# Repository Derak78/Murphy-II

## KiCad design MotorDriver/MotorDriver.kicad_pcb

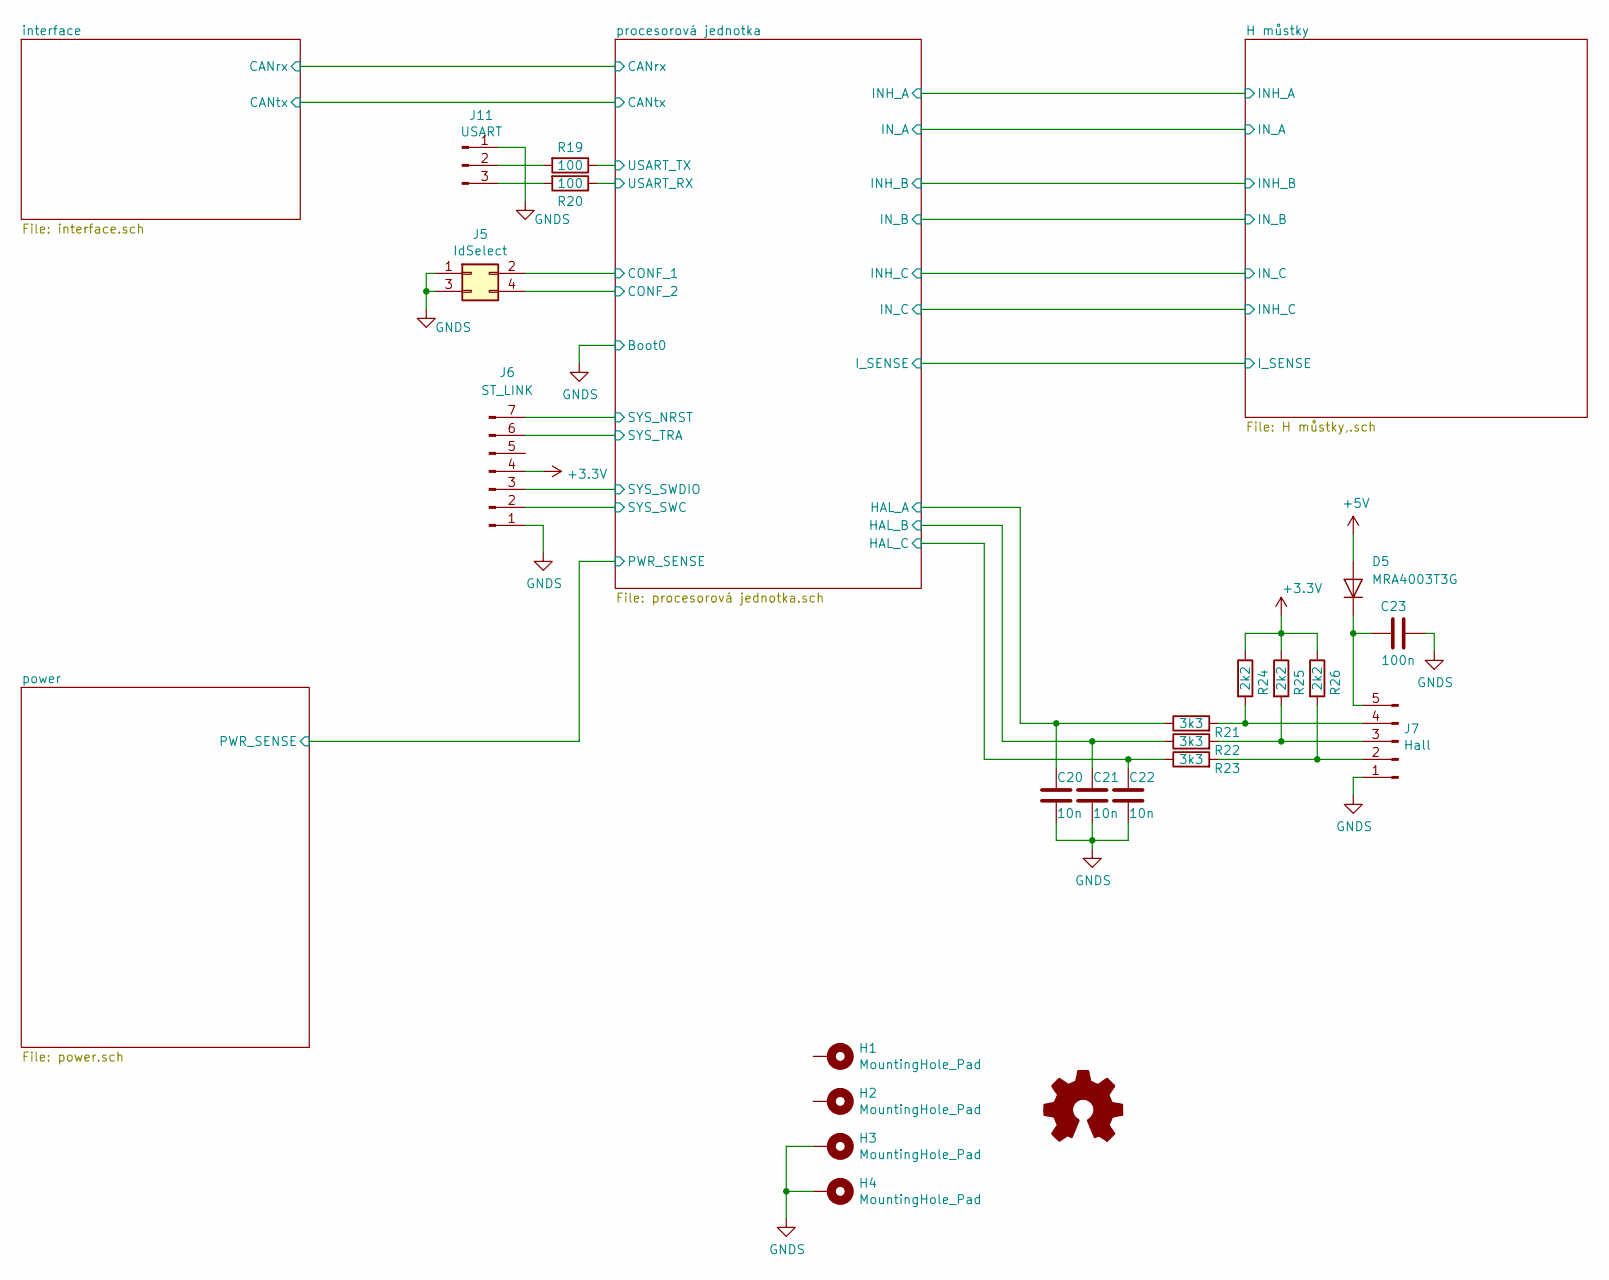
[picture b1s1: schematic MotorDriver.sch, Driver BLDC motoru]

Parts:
C20, C21, C22: 10n; C_0603_1608Metric_Pad1.05x0.95mm_HandSolder
C23: 100n; C_0603_1608Metric_Pad1.05x0.95mm_HandSolder
D5: MRA4003T3G; D_SMA-SMB_Universal_Handsoldering
H1, H2, H3, H4: MountingHole_Pad; MountingHole_3.2mm_M3_Pad
J5: IdSelect; PinHeader_2x02_P2.54mm_Vertical
J6: ST_LINK; PinHeader_1x07_P2.54mm_Vertical
J7: Hall; Molex_KK-254_AE-6410-05A_1x05_P2.54mm_Vertical
J11: USART; PinHeader_1x03_P2.54mm_Vertical
R19, R20: 100; R_0603_1608Metric_Pad1.05x0.95mm_HandSolder
R21, R22, R23: 3k3; R_0603_1608Metric_Pad1.05x0.95mm_HandSolder
R24, R25, R26: 2k2; R_0603_1608Metric_Pad1.05x0.95mm_HandSolder

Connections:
+3V3: J6.4, R24.1, R25.1, R26.1; also elsewhere on the board
+5V: D5.2 (A); also elsewhere on the board
/procesorová jednotka/CONF_1: J5.2; also elsewhere on the board
/procesorová jednotka/CONF_2: J5.4; also elsewhere on the board
/procesorová jednotka/HAL_A: C20.1, R21.1; also elsewhere on the board
/procesorová jednotka/HAL_B: C21.1, R22.1; also elsewhere on the board
/procesorová jednotka/HAL_C: C22.1, R23.1; also elsewhere on the board
/procesorová jednotka/SYS_NRST: J6.7; also elsewhere on the board
/procesorová jednotka/SYS_SWC: J6.2; also elsewhere on the board
/procesorová jednotka/SYS_SWDIO: J6.3; also elsewhere on the board
/procesorová jednotka/SYS_TRA: J6.6; also elsewhere on the board
/procesorová jednotka/USART_RX: R20.1; also elsewhere on the board
/procesorová jednotka/USART_TX: R19.1; also elsewhere on the board
GNDS: C20.2, C21.2, C22.2, C23.2, H3.1, H4.1, J5.1, J5.3, J6.1, J7.1, J11.1; also elsewhere on the board
unnamed: C23.1, D5.1 (K), J7.5
unnamed: J7.2, R23.2, R26.2
unnamed: J7.3, R22.2, R25.2
unnamed: J7.4, R21.2, R24.2
unnamed: J11.2, R19.2
unnamed: J11.3, R20.2

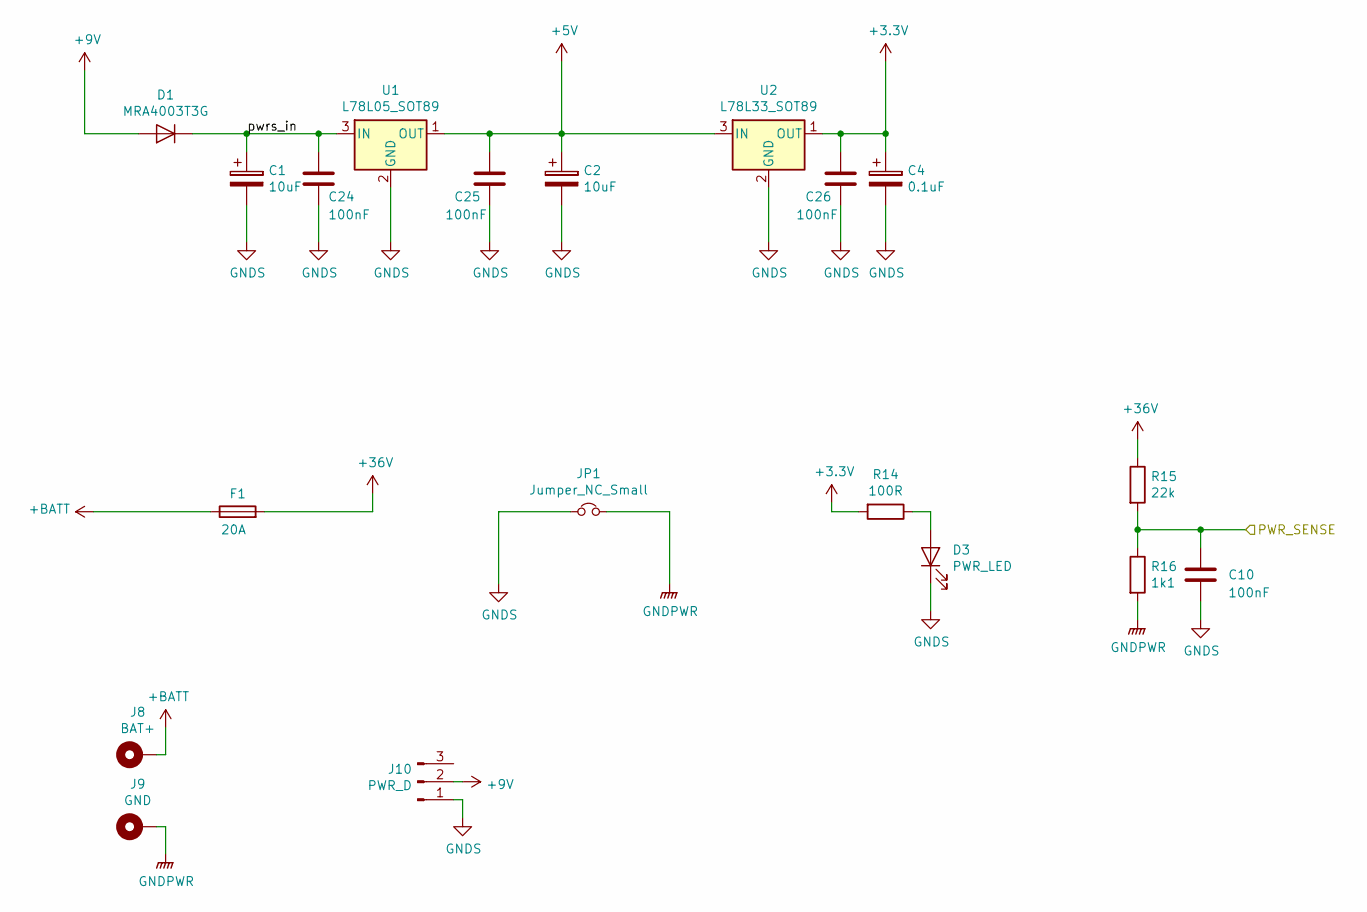
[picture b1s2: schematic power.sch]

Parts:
C1, C2: 10uF; CP_Elec_4x5.4
C4: 0.1uF; CP_Elec_4x5.4
C10, C24, C25, C26: 100nF; C_0603_1608Metric_Pad1.05x0.95mm_HandSolder
D1: MRA4003T3G; D_SMA-SMB_Universal_Handsoldering
D3: PWR_LED; LED_D3.0mm_Clear
F1: 20A; Fuseholder_Blade_Mini_Keystone_3568
J8: BAT+; MountingHole_2.2mm_M2_Pad_Via
J9: GND; MountingHole_2.2mm_M2_Pad_Via
J10: PWR_D; Molex_KK-254_AE-6410-03A_1x03_P2.54mm_Vertical
JP1: Jumper_NC_Small; SolderJumper-2_P1.3mm_Open_RoundedPad1.0x1.5mm
R14: 100R; R_0603_1608Metric_Pad1.05x0.95mm_HandSolder
R15: 22k; R_0603_1608Metric_Pad1.05x0.95mm_HandSolder
R16: 1k1; R_0603_1608Metric_Pad1.05x0.95mm_HandSolder
U1: L78L05_SOT89; SOT-89-3
U2: L78L33_SOT89; SOT-89-3

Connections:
+3V3: C4.1, C26.1, R14.2, U2.1 (OUT); also elsewhere on the board
+5V: C2.1, C25.1, U1.1 (OUT), U2.3 (IN); also elsewhere on the board
+9V: D1.2 (A), J10.2
+36V: F1.2, R15.1; also elsewhere on the board
+BATT: F1.1, J8.1
/power/PWR_SENSE: C10.1, R15.2, R16.1; also elsewhere on the board
/power/pwrs_in: C1.1, C24.1, D1.1 (K), U1.3 (IN)
GNDPWR: J9.1, JP1.2, R16.2; also elsewhere on the board
GNDS: C1.2, C2.2, C4.2, C10.2, C24.2, C25.2, C26.2, D3.1 (K), J10.1, JP1.1, U1.2 (GND), U2.2 (GND); also elsewhere on the board
unnamed: D3.2 (A), R14.1

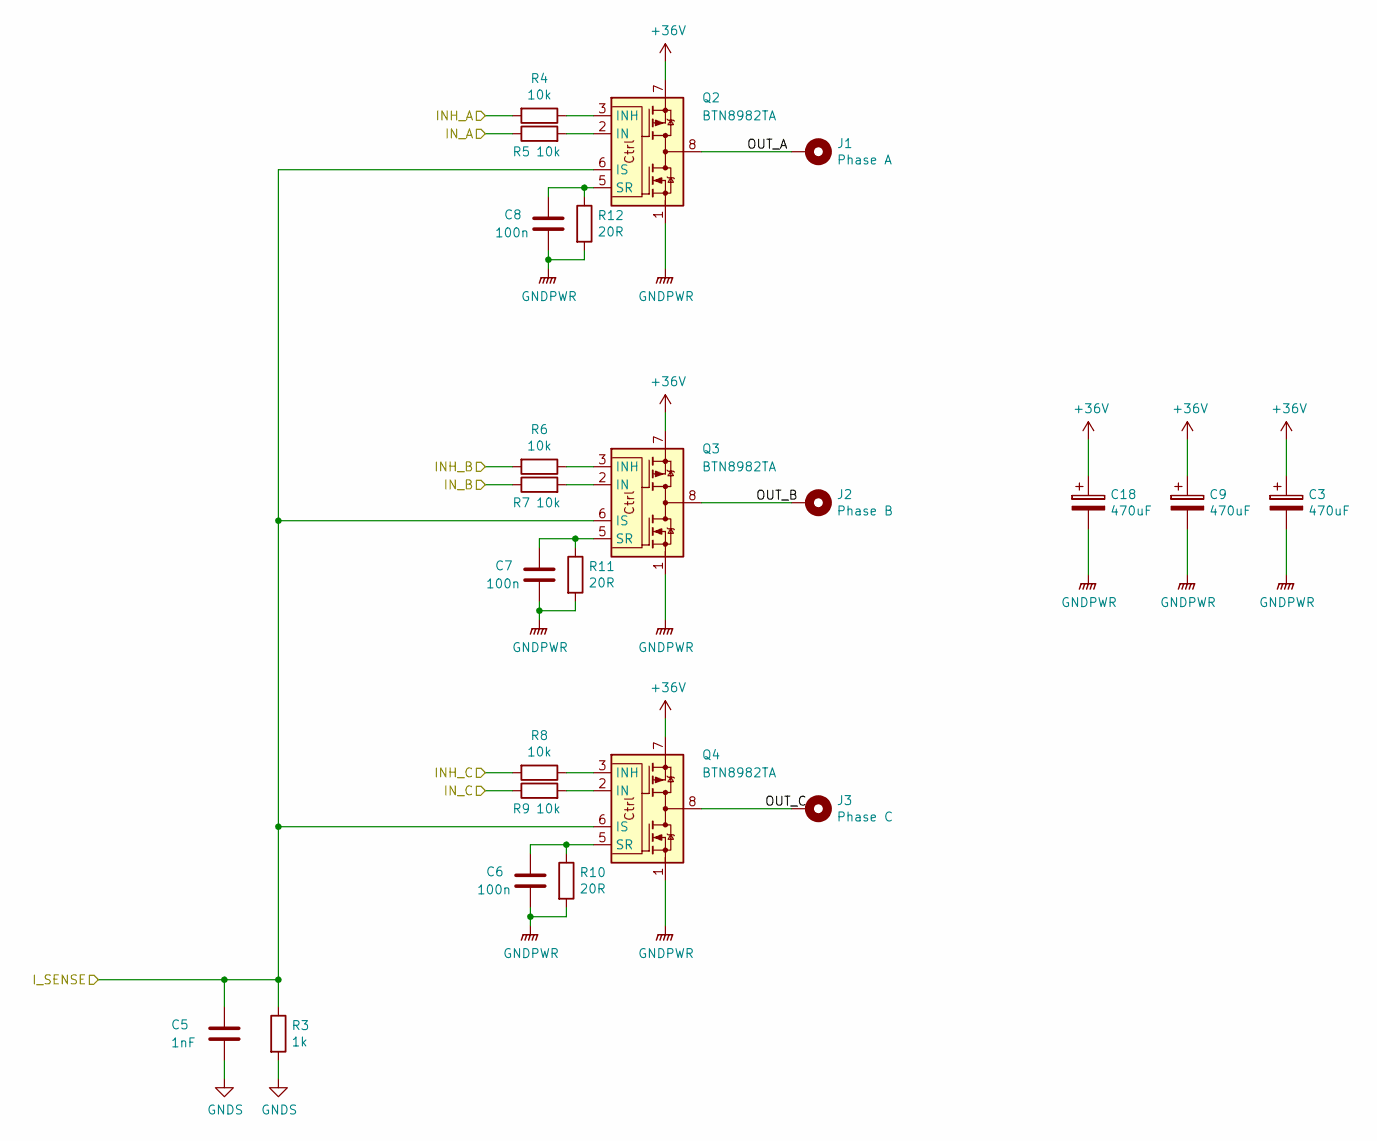
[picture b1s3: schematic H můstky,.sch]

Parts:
C3, C9: 470uF; CP_Radial_D12.5mm_P5.00mm
C5: 1nF; C_0603_1608Metric_Pad1.05x0.95mm_HandSolder
C6, C7, C8: 100n; C_0603_1608Metric_Pad1.05x0.95mm_HandSolder
C18: 470uF; CP_Radial_D12.5mm_P7.50mm
J1: Phase A; MountingHole_2.2mm_M2_Pad_Via
J2: Phase B; MountingHole_2.2mm_M2_Pad_Via
J3: Phase C; MountingHole_2.2mm_M2_Pad_Via
Q2, Q3, Q4: BTN8982TA; TO-263-7_TabPin8
R3: 1k; R_0603_1608Metric_Pad1.05x0.95mm_HandSolder
R4, R5, R6, R7, R8, R9: 10k; R_0603_1608Metric_Pad1.05x0.95mm_HandSolder
R10, R11, R12: 20R; R_0603_1608Metric_Pad1.05x0.95mm_HandSolder

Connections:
+36V: C3.1, C9.1, C18.1, Q2.7, Q3.7, Q4.7; also elsewhere on the board
/H můstky/INH_A: R4.2; also elsewhere on the board
/H můstky/INH_B: R6.2; also elsewhere on the board
/H můstky/INH_C: R8.2; also elsewhere on the board
/H můstky/IN_A: R5.1; also elsewhere on the board
/H můstky/IN_B: R7.1; also elsewhere on the board
/H můstky/I_SENSE: C5.1, Q2.6 (IS), Q3.6 (IS), Q4.6 (IS), R3.1; also elsewhere on the board
/H můstky/OUT_A: J1.1, Q2.4, Q2.8
/H můstky/OUT_B: J2.1, Q3.4, Q3.8
/H můstky/OUT_C: J3.1, Q4.4, Q4.8
/procesorová jednotka/INH_C: R9.1; also elsewhere on the board
GNDPWR: C3.2, C6.2, C7.2, C8.2, C9.2, C18.2, Q2.1, Q3.1, Q4.1, R10.2, R11.2, R12.2; also elsewhere on the board
GNDS: C5.2, R3.2; also elsewhere on the board
unnamed: C6.1, Q4.5 (SR), R10.1
unnamed: C7.1, Q3.5 (SR), R11.1
unnamed: C8.1, Q2.5 (SR), R12.1
unnamed: Q2.2 (IN), R5.2
unnamed: Q2.3 (INH), R4.1
unnamed: Q3.2 (IN), R7.2
unnamed: Q3.3 (INH), R6.1
unnamed: Q4.2 (IN), R9.2
unnamed: Q4.3 (INH), R8.1

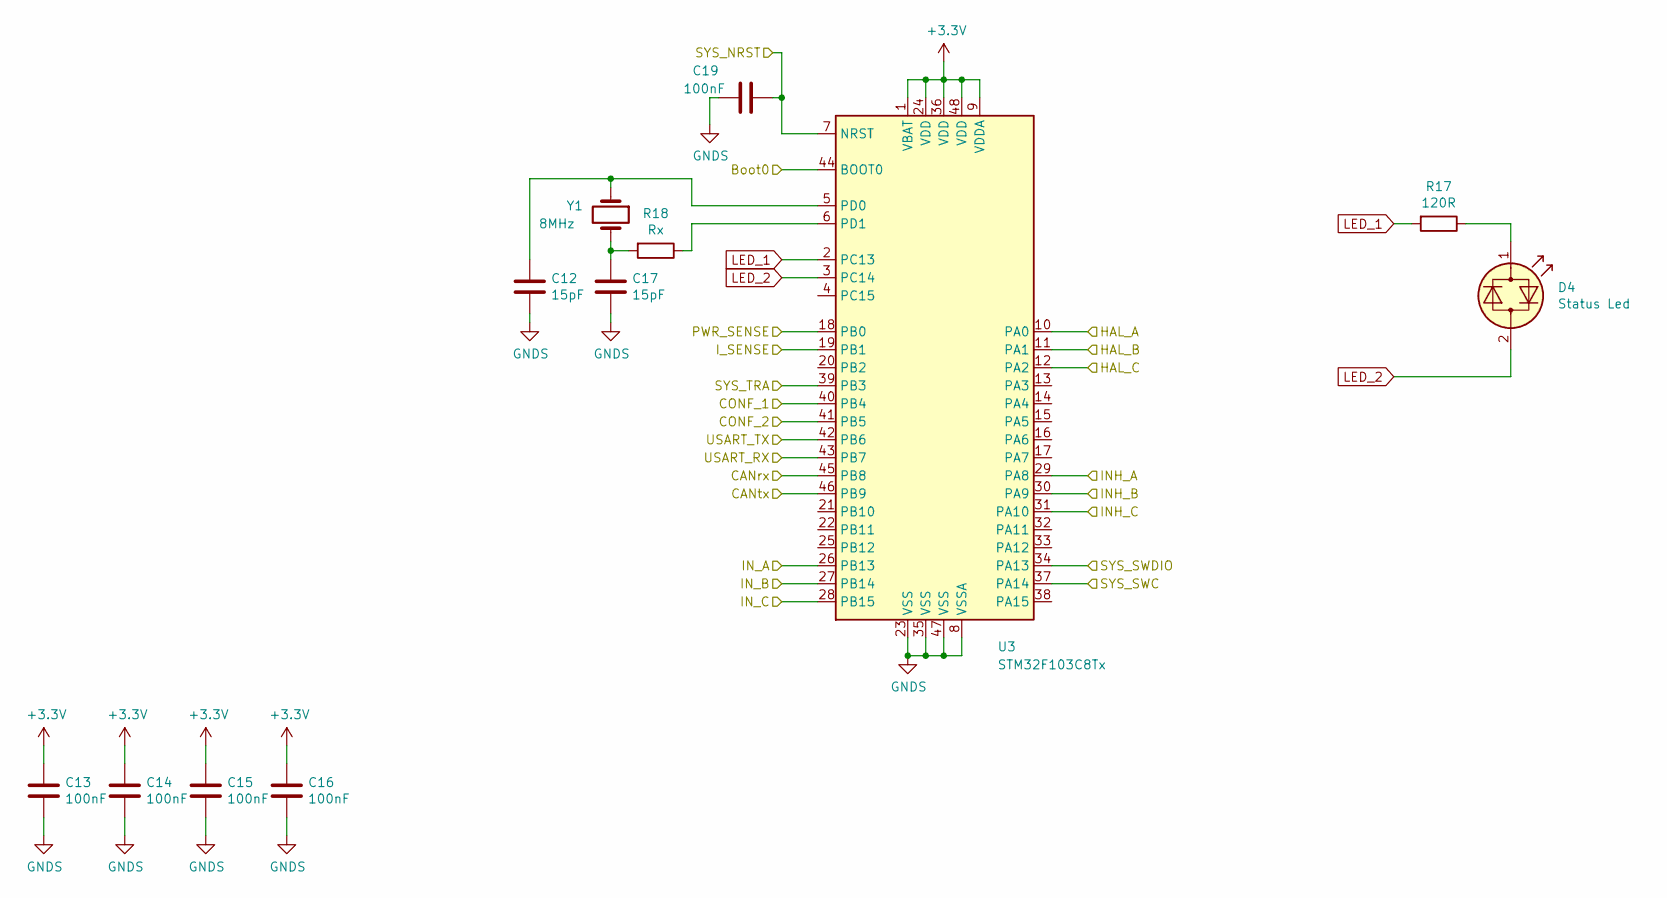
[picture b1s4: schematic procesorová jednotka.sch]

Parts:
C12, C17: 15pF; C_0603_1608Metric_Pad1.05x0.95mm_HandSolder
C13, C14, C15, C16, C19: 100nF; C_0603_1608Metric_Pad1.05x0.95mm_HandSolder
D4: Status Led; LED_D3.0mm_Clear
R17: 120R; R_0603_1608Metric_Pad1.05x0.95mm_HandSolder
R18: Rx; R_0603_1608Metric_Pad1.05x0.95mm_HandSolder
U3: STM32F103C8Tx; LQFP-48_7x7mm_P0.5mm
Y1: 8MHz; Crystal_HC49-4H_Vertical

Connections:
+3V3: C13.1, C14.1, C15.1, C16.1, U3.1 (VBAT), U3.9 (VDDA), U3.24 (VDD), U3.36 (VDD), U3.48 (VDD); also elsewhere on the board
/H můstky/INH_A: U3.29 (PA8); also elsewhere on the board
/H můstky/INH_B: U3.30 (PA9); also elsewhere on the board
/H můstky/INH_C: U3.28 (PB15); also elsewhere on the board
/H můstky/IN_A: U3.26 (PB13); also elsewhere on the board
/H můstky/IN_B: U3.27 (PB14); also elsewhere on the board
/H můstky/I_SENSE: U3.19 (PB1); also elsewhere on the board
/interface/CANrx: U3.45 (PB8); also elsewhere on the board
/interface/CANtx: U3.46 (PB9); also elsewhere on the board
/power/PWR_SENSE: U3.18 (PB0); also elsewhere on the board
/procesorová jednotka/CONF_1: U3.40 (PB4); also elsewhere on the board
/procesorová jednotka/CONF_2: U3.41 (PB5); also elsewhere on the board
/procesorová jednotka/HAL_A: U3.10 (PA0); also elsewhere on the board
/procesorová jednotka/HAL_B: U3.11 (PA1); also elsewhere on the board
/procesorová jednotka/HAL_C: U3.12 (PA2); also elsewhere on the board
/procesorová jednotka/INH_C: U3.31 (PA10); also elsewhere on the board
/procesorová jednotka/SYS_NRST: C19.1, U3.7 (NRST); also elsewhere on the board
/procesorová jednotka/SYS_SWC: U3.37 (PA14); also elsewhere on the board
/procesorová jednotka/SYS_SWDIO: U3.34 (PA13); also elsewhere on the board
/procesorová jednotka/SYS_TRA: U3.39 (PB3); also elsewhere on the board
/procesorová jednotka/USART_RX: U3.43 (PB7); also elsewhere on the board
/procesorová jednotka/USART_TX: U3.42 (PB6); also elsewhere on the board
GNDS: C12.2, C13.2, C14.2, C15.2, C16.2, C17.2, C19.2, U3.8 (VSSA), U3.23 (VSS), U3.35 (VSS), U3.44 (BOOT0), U3.47 (VSS); also elsewhere on the board
LED_1: R17.2, U3.2 (PC13)
LED_2: D4.2 (AK), U3.3 (PC14)
unnamed: C12.1, U3.5 (PD0), Y1.1
unnamed: C17.1, R18.2, Y1.2
unnamed: D4.1 (KA), R17.1
unnamed: R18.1, U3.6 (PD1)

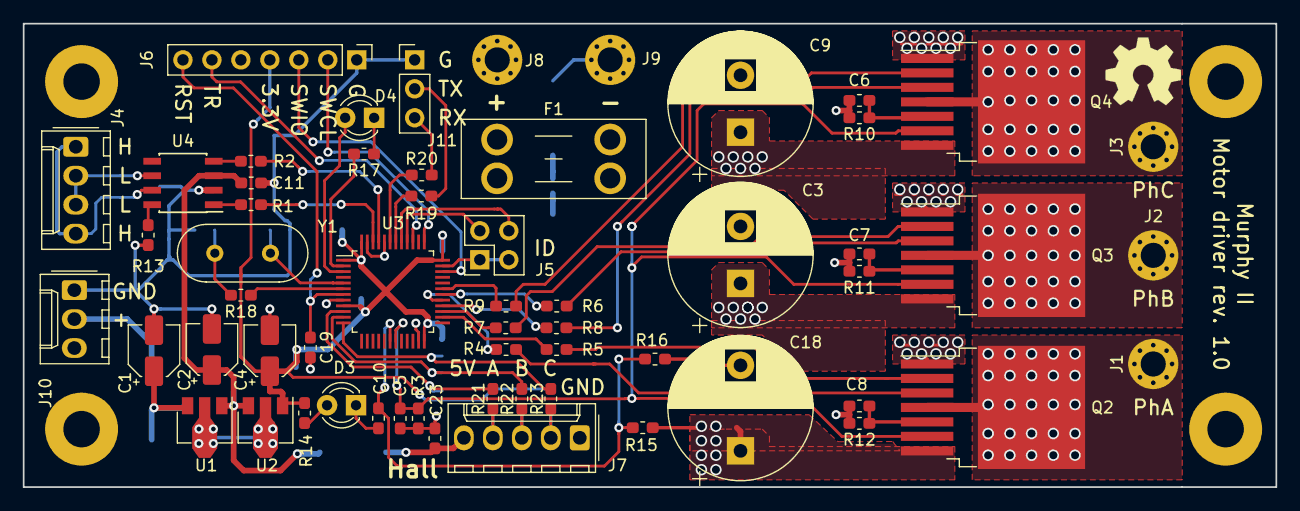
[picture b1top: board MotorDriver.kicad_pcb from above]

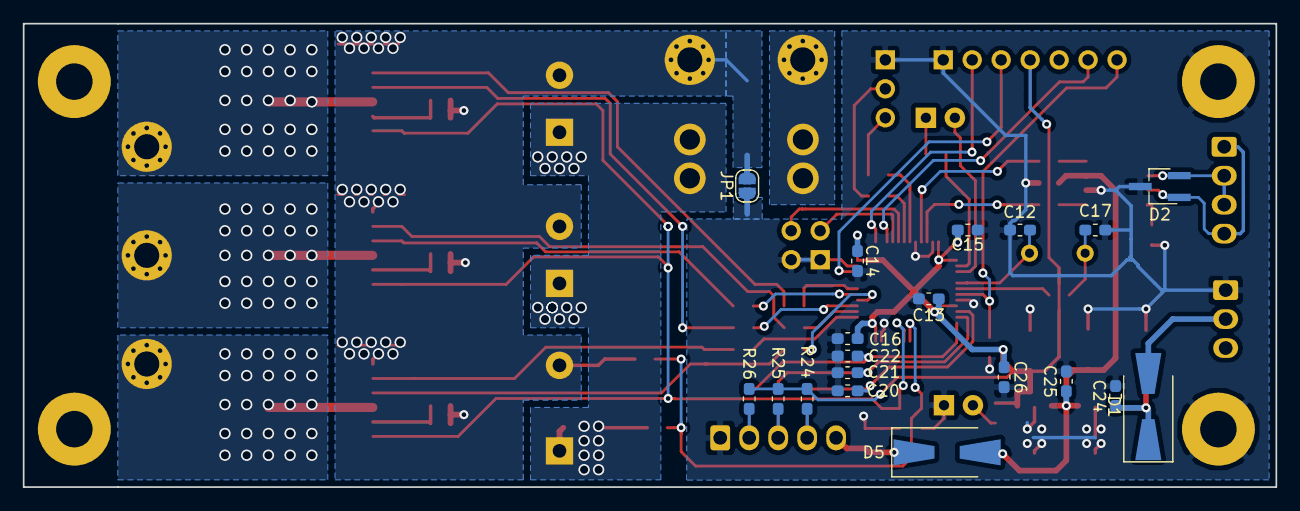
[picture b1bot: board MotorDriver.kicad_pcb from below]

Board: 2 copper layers, 109.9 x 40.6 mm, 82 parts (19 on the bottom side), 59 nets.

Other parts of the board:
C11: 100nF; C_0603_1608Metric_Pad1.05x0.95mm_HandSolder
D2: PESD1CAN; TSOT-23_HandSoldering
J4: CAN; Molex_KK-254_AE-6410-04A_1x04_P2.54mm_Vertical
R1, R2: 1k; R_0603_1608Metric_Pad1.05x0.95mm_HandSolder
R13: 10k; R_0603_1608Metric_Pad1.05x0.95mm_HandSolder
U4: MCP2551-I-SN; SOIC-8_3.9x4.9mm_P1.27mm

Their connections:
+5V: C11.1, U4.3; also elsewhere on the board
/interface/CANrx: R2.2; also elsewhere on the board
/interface/CANtx: R1.2; also elsewhere on the board
GNDS: C11.2, D2.3, R13.2, U4.2; also elsewhere on the board
unnamed: D2.1, J4.1, J4.4, U4.7
unnamed: D2.2, J4.2, J4.3, U4.6
unnamed: R1.1, U4.1
unnamed: R2.1, U4.4
unnamed: R13.1, U4.8

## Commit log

2019-01-04 Robot model
2019-01-24 Finished printable parts
2019-01-26 Power and output ping changed roblaced by holes. Correction of tracks width and vias diameters.
2019-01-27 Added filter capacitors to low votlage power supply
